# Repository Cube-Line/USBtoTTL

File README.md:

# USB转串口小工具硬件
发现大多数TB的USB串口工具老出各种意外,于是自己画了一版.
* 主控芯片使用CP2104,通讯速率最大可达2Mbps.
* 集成了功率开关-BD2243G-GTR(限流500mA)
* 集成电源和过功率指示灯、接收发送指示灯.
* USB口添加ESD保护-BDFN1710A054U.
* 添加3.3V线性稳压器，支持3V3逻辑电平.
* 添加DTR流控制，支持Arduino自动下载.

## 仿真图
* TOP  
  
* BOTTOM

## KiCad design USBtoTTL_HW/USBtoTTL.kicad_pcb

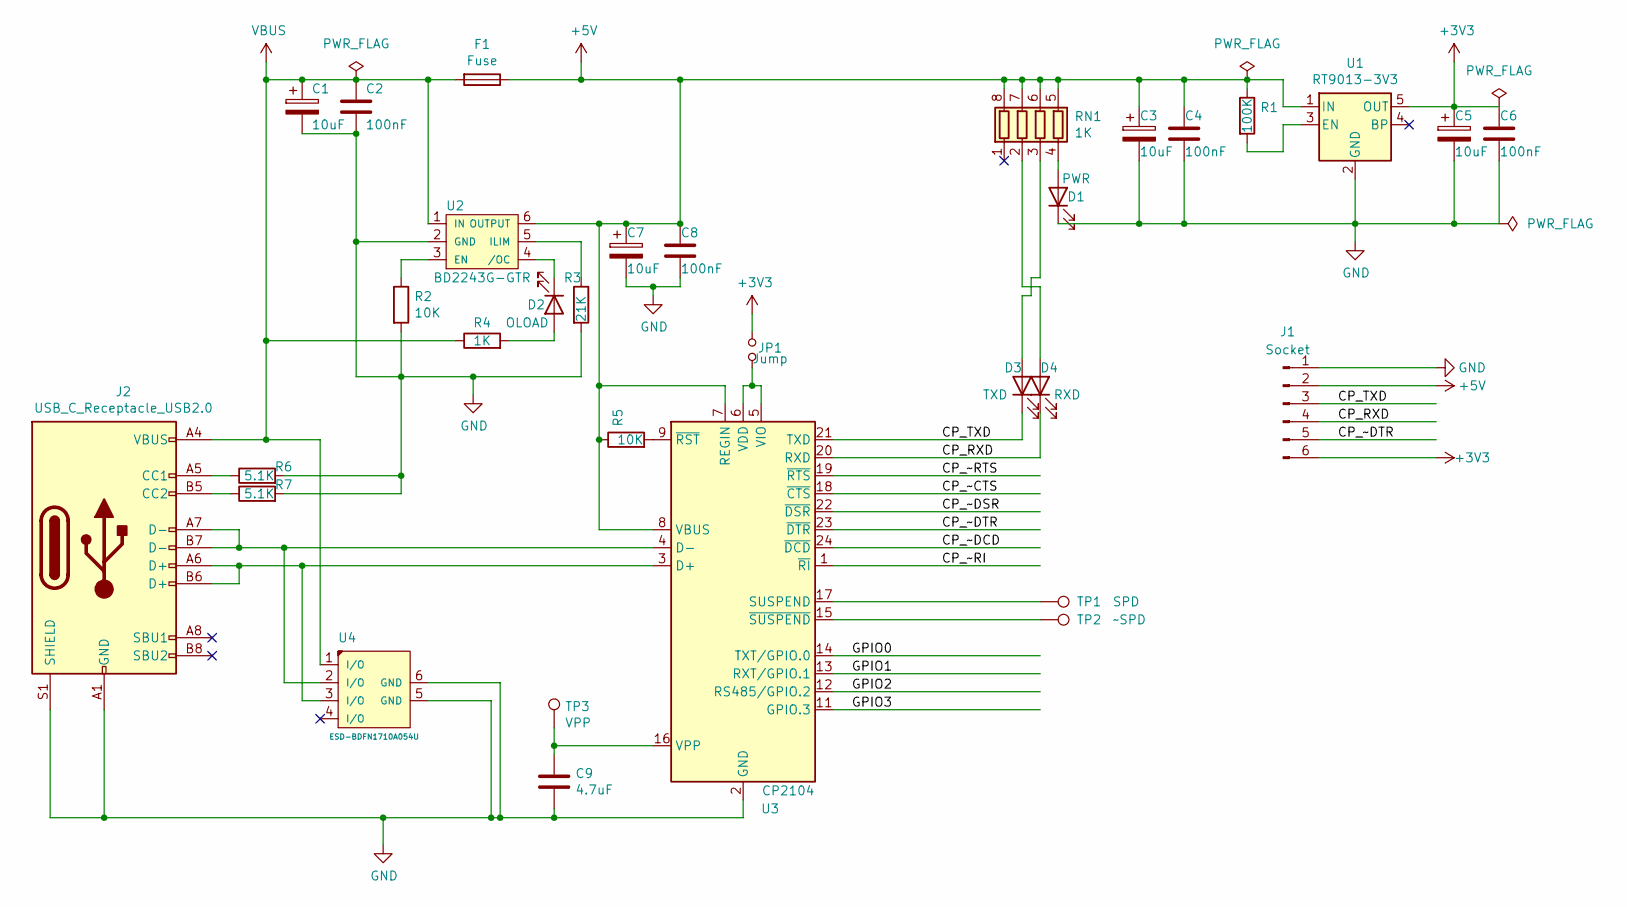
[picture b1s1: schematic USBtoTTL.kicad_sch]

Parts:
C1: 10uF; CP_EIA-3216-10_Kemet-I
C2, C4, C6, C8: 100nF; C_0402_1005Metric
C3, C5, C7: 10uF; C_0603_1608Metric
C9: 4.7uF; C_0402_1005Metric
D1: PWR; LED_0402_1005Metric
D2: OLOAD; LED_0402_1005Metric
D3: TXD; LED_0402_1005Metric
D4: RXD; LED_0402_1005Metric
F1: Fuse; Fuse_0805_2012Metric
J1: Socket; Harwin_M20-89006xx_1x06_P2.54mm_Horizontal
J2: USB_C_Receptacle_USB2.0; USB_C_Receptacle_HRO_TYPE-C-31-M-12
JP1: Jump; JUMP_OPEN_2P_0.3MMx0.5MM
R1: 100K; R_0402_1005Metric
R2, R5: 10K; R_0402_1005Metric
R3: 21K; R_0402_1005Metric
R4: 1K; R_0402_1005Metric
R6, R7: 5.1K; R_0402_1005Metric
RN1: 1K; R_Array_Concave_4x0402
TP1: SPD; TestPoint_Pad_D1.0mm
TP2: ~SPD; TestPoint_Pad_D1.0mm
TP3: VPP; TestPoint_Pad_D1.0mm
U1: RT9013-3V3; SOT-23-5
U2: BD2243G-GTR; SOT-23-6
U3: CP2104; QFN-24-1EP_4x4mm_P0.5mm_EP2.6x2.6mm
U4: ESD-BDFN1710A054U; DFN1710-6

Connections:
+3V3: C5.1, C6.1, J1.6, JP1.2, U1.5 (OUT)
+5V: C3.1, C4.1, C7.1, C8.1, F1.1, J1.2, R1.1, R5.1, RN1.5 (R4.2), RN1.6 (R3.2), RN1.7 (R2.2), RN1.8 (R1.2), U1.1 (IN), U2.6 (OUTPUT), U3.7 (REGIN), U3.8 (VBUS)
/CP_RXD: D4.1 (K), J1.4, U3.20 (RXD)
/CP_TXD: D3.1 (K), J1.3, U3.21 (TXD)
/CP_~CTS: U3.18 (~CTS)
/CP_~DCD: U3.24 (~DCD)
/CP_~DSR: U3.22 (~DSR)
/CP_~DTR: J1.5, U3.23 (~DTR)
/CP_~RI: U3.1 (~RI)
/CP_~RTS: U3.19 (~RTS)
/GPIO0: U3.14 (TXT/GPIO.0)
/GPIO1: U3.13 (RXT/GPIO.1)
/GPIO2: U3.12 (RS485/GPIO.2)
/GPIO3: U3.11 (GPIO.3)
GND: C1.2, C2.2, C3.2, C4.2, C5.2, C6.2, C7.2, C8.2, C9.2, D1.1 (K), J1.1, J2.A1 (GND), J2.A12 (GND), J2.B1 (GND), J2.B12 (GND), J2.S1 (SHIELD), R2.2, R3.2, R6.2, R7.2, U1.2 (GND), U2.2 (GND), U3.2 (GND), U3.25 (GND), U4.5 (GND), U4.6 (GND)
unnamed: C9.1, TP3.1, U3.16 (VPP)
unnamed: D1.2 (A), RN1.4 (R4.1)
unnamed: D2.1 (K), U2.4 (/OC)
unnamed: D2.2 (A), R4.2
unnamed: D3.2 (A), RN1.3 (R3.1)
unnamed: D4.2 (A), RN1.2 (R2.1)
unnamed: J2.A5 (CC1), R6.1
unnamed: J2.A6 (D+), J2.B6 (D+), U3.3 (D+), U4.3 (I/O)
unnamed: J2.A7 (D-), J2.B7 (D-), U3.4 (D-), U4.2 (I/O)
unnamed: J2.B5 (CC2), R7.1
unnamed: JP1.1, U3.5 (VIO), U3.6 (VDD)
unnamed: R1.2, U1.3 (EN)
unnamed: R2.1, U2.3 (EN)
unnamed: R3.1, U2.5 (ILIM)
unnamed: R5.2, U3.9 (~RST)
unnamed: TP1.1, U3.17 (SUSPEND)
unnamed: TP2.1, U3.15 (~SUSPEND)
VBUS: C1.1, C2.1, F1.2, J2.A4 (VBUS), J2.A9 (VBUS), J2.B4 (VBUS), J2.B9 (VBUS), R4.1, U2.1 (IN), U4.1 (I/O)

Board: 4 copper layers, 32 parts (4 on the bottom side), 24 nets, no tracks yet.

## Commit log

2022-04-27 首次提交
2022-04-27 更新README.md
2022-07-21 修复一些bug
